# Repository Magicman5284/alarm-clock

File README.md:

Welcome to my alarm clock!

This project is an alarm clock that runs on an ESP32 and is controlled using an apple shortcut
The shortcut can be found here: https://www.icloud.com/shortcuts/9c18b0a72f074b27aea9341c8937683c

Features:
Set alarm
Set repeating alarm
View alarm list
cancel alarm
stopwatch
timer
cancel alarm

About the design:
The PCB has a bunch of little bits of text and images over because I decided to customize it
This is the third PCB I've made, and it's the first one I went all out on decorating. 
Look around for some of the easter eggs!

Use:
Useage is pretty simple, just run the short cut and it gives you prompts from there. 
your phone needs to be on the same wifi network in order to connect
Pressing the button does different thing depending on what mode the cock is in
When pressing it when the clock is at idle, it will display the next alarm. 
When pressing it while a stop watch is running it will stop the stopwatch
When pressing it while a timer is running it will stop the timer. 
And obviously when pressing it while an alarm is going off it will stop the alarm. 

Assembly:
before uploading code, make sure to input your wifi details into the software
put all components except for the switch on the side with the dog
put the switch on the other side
I'm not gonna bother explaining how to solder
next, put the screen in the screen hole of the housing
put the speaker in the speaker hole of the housing
Put the PCB in the housing, making sure to align the port on the ESP32 with the hole
put the lid on 
put the keycap on the switch
power it using the port on the esp32

BOM: 
| Item                     | Qty | Supplier   | Cost/item | Total Cost | link                                                                                                                                                                                                                                                                                                                                                                                                                                                                                                                                                                                                                                                                   |
|--------------------------|-----|------------|-----------|------------|------------------------------------------------------------------------------------------------------------------------------------------------------------------------------------------------------------------------------------------------------------------------------------------------------------------------------------------------------------------------------------------------------------------------------------------------------------------------------------------------------------------------------------------------------------------------------------------------------------------------------------------------------------------------|
| PCB                      | 1   | JLCPCB     | $11.75    | $11.75     | https://cart.jlcpcb.com/shopcart/cart/                                                                                                                                                                                                                                                                                                                                                                                                                                                                                                                                                                                                                                 |
| ESP32 Devkit 32e         | 1   | Aliexpress | $4.89     | $4.89      | https://www.aliexpress.us/item/3256806702153769.html?spm=a2g0o.productlist.main.18.67585c09bSFoCP&algo_pvid=f1ce53f9-d5df-4b3a-970c-3f98776b2e6a&algo_exp_id=f1ce53f9-d5df-4b3a-970c-3f98776b2e6a-17&pdp_ext_f=%7B%22order%22%3A%22350%22%2C%22eval%22%3A%221%22%2C%22fromPage%22%3A%22search%22%7D&pdp_npi=6%40dis%21USD%213.09%213.09%21%21%213.09%213.09%21%40210311c217933246971303026e0ffa%2112000038626150028%21sea%21US%212783459362%21X%211%210%21n_tag%3A-29919%3Bd%3Abaf43391%3Bm03_new_user%3A-29895&curPageLogUid=7mRbqkwcirtO&utparam-url=scene%3Asearch%7Cquery_from%3A%7Cx_object_id%3A1005006888468521%7C_p_origin_prod%3A                             |
| dfplayermini             | 1   | Aliexpress | $0.99     | $0.99      | https://www.aliexpress.us/w/wholesale-dfplayermi.html?spm=a2g0o.cart.search.0                                                                                                                                                                                                                                                                                                                                                                                                                                                                                                                                                                                          |
| 4 ohm 3 watt speaker     | 1   | Aliexpress | $1.55     | $1.55      | https://www.aliexpress.us/item/3256808440309449.html?spm=a2g0o.productlist.main.26.3e115336ekZqeb&algo_pvid=ed21cef5-22ef-4ecc-961e-e51a669bdb40&algo_exp_id=ed21cef5-22ef-4ecc-961e-e51a669bdb40-25&pdp_ext_f=%7B%22order%22%3A%225833%22%2C%22eval%22%3A%221%22%2C%22fromPage%22%3A%22search%22%7D&pdp_npi=6%40dis%21USD%215.25%214.25%21%21%215.25%214.25%21%402101e81117933248692643231e0f08%2112000046009599177%21sea%21US%212783459362%21X%211%210%21n_tag%3A-29919%3Bd%3Abaf43391%3Bm03_new_user%3A-29895%3BpisId%3A5000000219603055&curPageLogUid=h7SvuAxJD4rP&utparam-url=scene%3Asearch%7Cquery_from%3A%7Cx_object_id%3A1005008626624201%7C_p_origin_prod%3A |
| cherry mx switch         | 1   | Aliexpress | $2.27     | $2.27      | https://www.aliexpress.us/item/3256801976570526.html?spm=a2g0o.productlist.main.5.688744ccV9ucZ5&algo_pvid=7ed89fed-d3cb-4a07-b618-00326d9a45f0&algo_exp_id=7ed89fed-d3cb-4a07-b618-00326d9a45f0-4&pdp_ext_f=%7B%22order%22%3A%2292%22%2C%22eval%22%3A%221%22%2C%22fromPage%22%3A%22search%22%7D&pdp_npi=6%40dis%21USD%212.27%212.27%21%21%212.27%212.27%21%402103274a17933249592103766e0baa%2112000018919108208%21sea%21US%212783459362%21X%211%210%21n_tag%3A-29919%3Bd%3Abaf43391%3Bm03_new_user%3A-29895&curPageLogUid=fu1PsmRXaU1L&utparam-url=scene%3Asearch%7Cquery_from%3A%7Cx_object_id%3A1005002162885278%7C_p_origin_prod%3A                                |
| 1x2 dupont connector     | 1   | Aliexpress | $1.60     | $1.60      | https://www.aliexpress.us/item/3256811876826434.html?spm=a2g0o.productlist.main.25.623949597420vA&algo_pvid=894fe34e-67f8-4acd-bffa-2217c9a293bd&algo_exp_id=894fe34e-67f8-4acd-bffa-2217c9a293bd-22&pdp_ext_f=%7B%22order%22%3A%22579%22%2C%22eval%22%3A%221%22%2C%22fromPage%22%3A%22search%22%7D&pdp_npi=6%40dis%21USD%212.60%211.60%21%21%212.60%211.60%21%402101e5ab17933250643156929e0eb4%2112000057466932456%21sea%21US%212783459362%21X%211%210%21n_tag%3A-29919%3Bd%3Abaf43391%3Bm03_new_user%3A-29895%3BpisId%3A5000000219603055&curPageLogUid=lbAIQ25zZsG3&utparam-url=scene%3Asearch%7Cquery_from%3A%7Cx_object_id%3A1005012063141186%7C_p_origin_prod%3A  |
| 1x4 dupont connector     | 1   | Aliexpress | $1.85     | $1.85      | https://www.aliexpress.us/item/3256811876826434.html?spm=a2g0o.productlist.main.25.623949597420vA&algo_pvid=894fe34e-67f8-4acd-bffa-2217c9a293bd&algo_exp_id=894fe34e-67f8-4acd-bffa-2217c9a293bd-22&pdp_ext_f=%7B%22order%22%3A%22579%22%2C%22eval%22%3A%221%22%2C%22fromPage%22%3A%22search%22%7D&pdp_npi=6%40dis%21USD%212.60%211.60%21%21%212.60%211.60%21%402101e5ab17933250643156929e0eb4%2112000057466932456%21sea%21US%212783459362%21X%211%210%21n_tag%3A-29919%3Bd%3Abaf43391%3Bm03_new_user%3A-29895%3BpisId%3A5000000219603055&curPageLogUid=lbAIQ25zZsG3&utparam-url=scene%3Asearch%7Cquery_from%3A%7Cx_object_id%3A1005012063141186%7C_p_origin_prod%3A  |
| 1k resistor              | 1   | Aliexpress | $0.99     | $0.99      | https://www.aliexpress.us/item/2251832129610568.html?spm=a2g0o.productlist.main.1.25326d60rdNL8u&algo_pvid=edfc57ec-6b59-4211-b7e8-f2a065aece70&algo_exp_id=edfc57ec-6b59-4211-b7e8-f2a065aece70-0&pdp_ext_f=%7B%22order%22%3A%22717%22%2C%22eval%22%3A%221%22%2C%22fromPage%22%3A%22search%22%7D&pdp_npi=6%40dis%21USD%211.47%210.99%21%21%211.47%210.99%21%402103094f17933252044222206e0fe1%2158254850883%21sea%21US%212783459362%21X%211%210%21n_tag%3A-29919%3Bd%3Abaf43391%3Bm03_new_user%3A-29895%3BpisId%3A5000000219603055&curPageLogUid=x9bjduV6E75j&utparam-url=scene%3Asearch%7Cquery_from%3A%7Cx_object_id%3A32315925320%7C_p_origin_prod%3A               |
| 2.75u keycap             | 1   | Aliexpress | $5.95     | $5.95      | https://www.aliexpress.us/item/3256807398966945.html?spm=a2g0o.productlist.main.2.5a3e4688DaLE72&algo_pvid=579fe484-0437-467e-8f6a-9ced1f6fc345&algo_exp_id=579fe484-0437-467e-8f6a-9ced1f6fc345-1&pdp_ext_f=%7B%22order%22%3A%22775%22%2C%22eval%22%3A%221%22%2C%22fromPage%22%3A%22search%22%7D&pdp_npi=6%40dis%21USD%215.95%215.95%21%21%2139.43%2139.43%21%402103094f17933252657634725e0fe1%2112000041398778703%21sea%21US%212783459362%21X%211%210%21n_tag%3A-29919%3Bd%3Abaf43391%3Bm03_new_user%3A-29895&curPageLogUid=ulMywThyTcc5&utparam-url=scene%3Asearch%7Cquery_from%3A%7Cx_object_id%3A1005007585281697%7C_p_origin_prod%3A                             |
| MicroSD card             | 1   | Aliexpress | $4.69     | $4.69      | https://www.aliexpress.us/item/3256811941680244.html?spm=a2g0o.productlist.main.8.60f66b2efRxJoC&algo_pvid=11c2aabe-f7a2-40ce-a041-4d8680cf8152&algo_exp_id=11c2aabe-f7a2-40ce-a041-4d8680cf8152-7&pdp_ext_f=%7B%22order%22%3A%22122%22%2C%22eval%22%3A%221%22%2C%22fromPage%22%3A%22search%22%7D&pdp_npi=6%40dis%21USD%214.75%214.65%21%21%2131.48%2130.82%21%40210328df17933253806557798e0f2b%2112000057588136790%21sea%21US%212783459362%21X%211%210%21n_tag%3A-29919%3Bd%3Abaf43391%3Bm03_new_user%3A-29895&curPageLogUid=MspO1k5kvHQz&utparam-url=scene%3Asearch%7Cquery_from%3A%7Cx_object_id%3A1005012127994996%7C_p_origin_prod%3A                             |
| TM1637 display           | 1   | Aliexpress | $1.51     | $1.51      | https://www.aliexpress.us/item/3256802087257562.html?spm=a2g0o.productlist.main.13.6d5a753f3vqx8d&algo_pvid=2fb0a497-69e9-4dab-829a-9f21d02ad9ce&algo_exp_id=2fb0a497-69e9-4dab-829a-9f21d02ad9ce-12&pdp_ext_f=%7B%22order%22%3A%2234%22%2C%22eval%22%3A%221%22%2C%22fromPage%22%3A%22search%22%7D&pdp_npi=6%40dis%21USD%211.51%211.51%21%21%211.51%211.51%21%40210327ef17933255281251190e0cd9%2112000019863214642%21sea%21US%212783459362%21X%211%210%21n_tag%3A-29919%3Bd%3Abaf43391%3Bm03_new_user%3A-29895&curPageLogUid=QMSImAcfJLqn&utparam-url=scene%3Asearch%7Cquery_from%3A%7Cx_object_id%3A1005002273572314%7C_p_origin_prod%3A                              |
| Estimated total shipping | 1   |            |           | $0.00      |                                                                                                                                                                                                                                                                                                                                                                                                                                                                                                                                                                                                                                                                        |

Images:

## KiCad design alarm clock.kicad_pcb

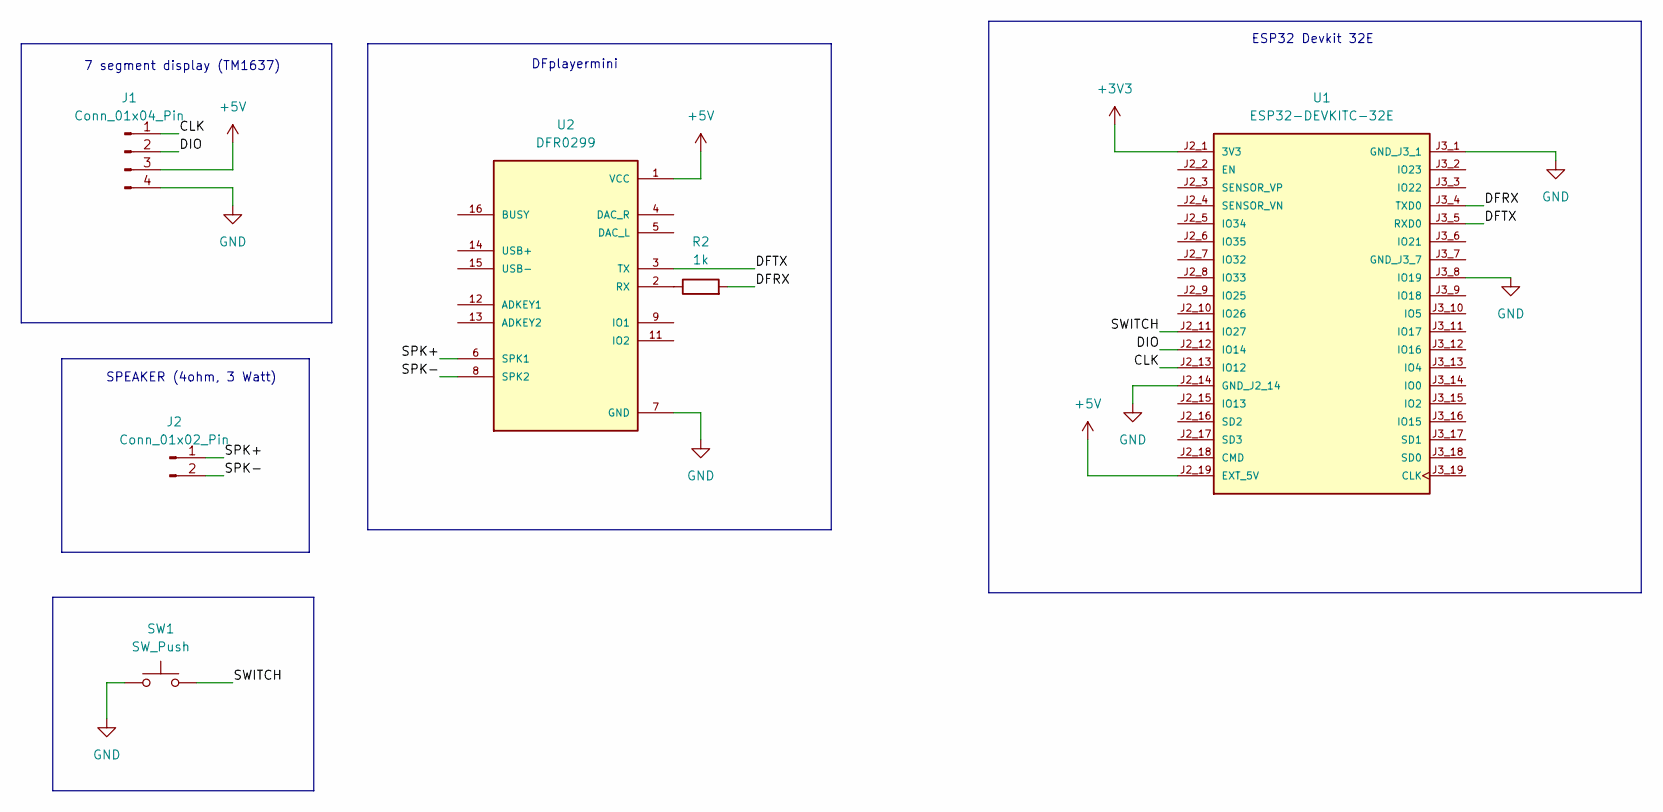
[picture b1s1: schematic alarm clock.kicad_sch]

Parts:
J1: Conn_01x04_Pin; PinSocket_1x04_P2.54mm_Vertical
J2: Conn_01x02_Pin; PinSocket_1x02_P2.54mm_Vertical
R2: 1k; R_Axial_DIN0204_L3.6mm_D1.6mm_P7.62mm_Horizontal
SW1: SW_Push; SW_Cherry_MX_1.00u_PCB
U1: ESP32-DEVKITC-32E; MODULE_ESP32-DEVKITC-32E; PARTREV 1.4
U2: DFR0299; MODULE_DFR0299; DigiKey_Part_Number 1738-1041-ND

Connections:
+3V3: U1.J2_1 (3V3)
+5V: J1.3, U1.J2_19 (EXT_5V), U2.1 (VCC)
/CLK: J1.1, U1.J2_13 (IO12)
/DFRX: R2.2, U1.J3_4 (TXD0)
/DFTX: U1.J3_5 (RXD0), U2.3 (TX)
/DIO: J1.2, U1.J2_12 (IO14)
/SPK+: J2.1, U2.6 (SPK1)
/SPK-: J2.2, U2.8 (SPK2)
/SWITCH: SW1.2, U1.J2_11 (IO27)
GND: J1.4, SW1.1, U1.J2_14 (GND_J2_14), U1.J3_1 (GND_J3_1), U1.J3_8 (IO19), U2.7 (GND), U2.10 (GND)
unnamed: R2.1, U2.2 (RX)

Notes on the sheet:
DFplayermini
7 segment display (TM1637)
SPEAKER (4ohm, 3 Watt)
ESP32 Devkit 32E

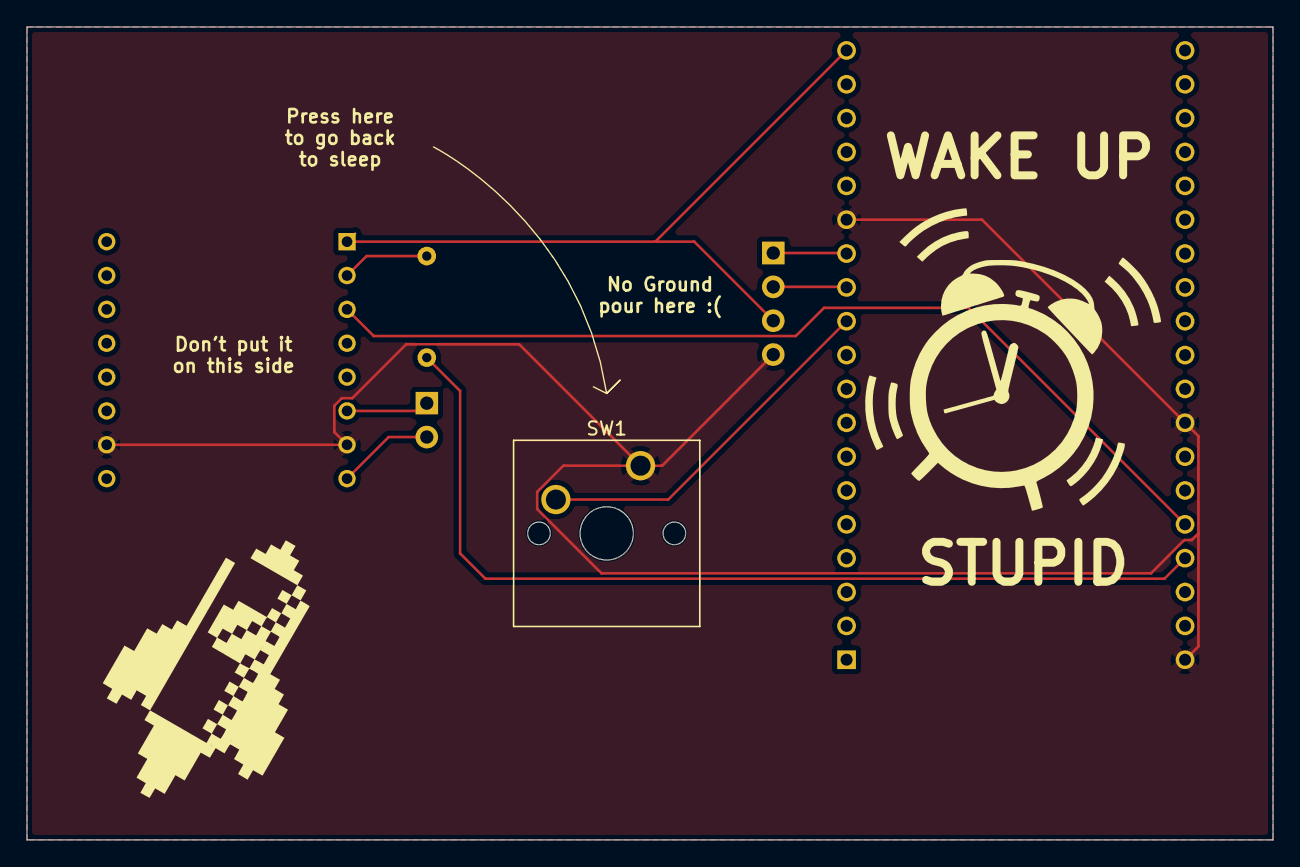
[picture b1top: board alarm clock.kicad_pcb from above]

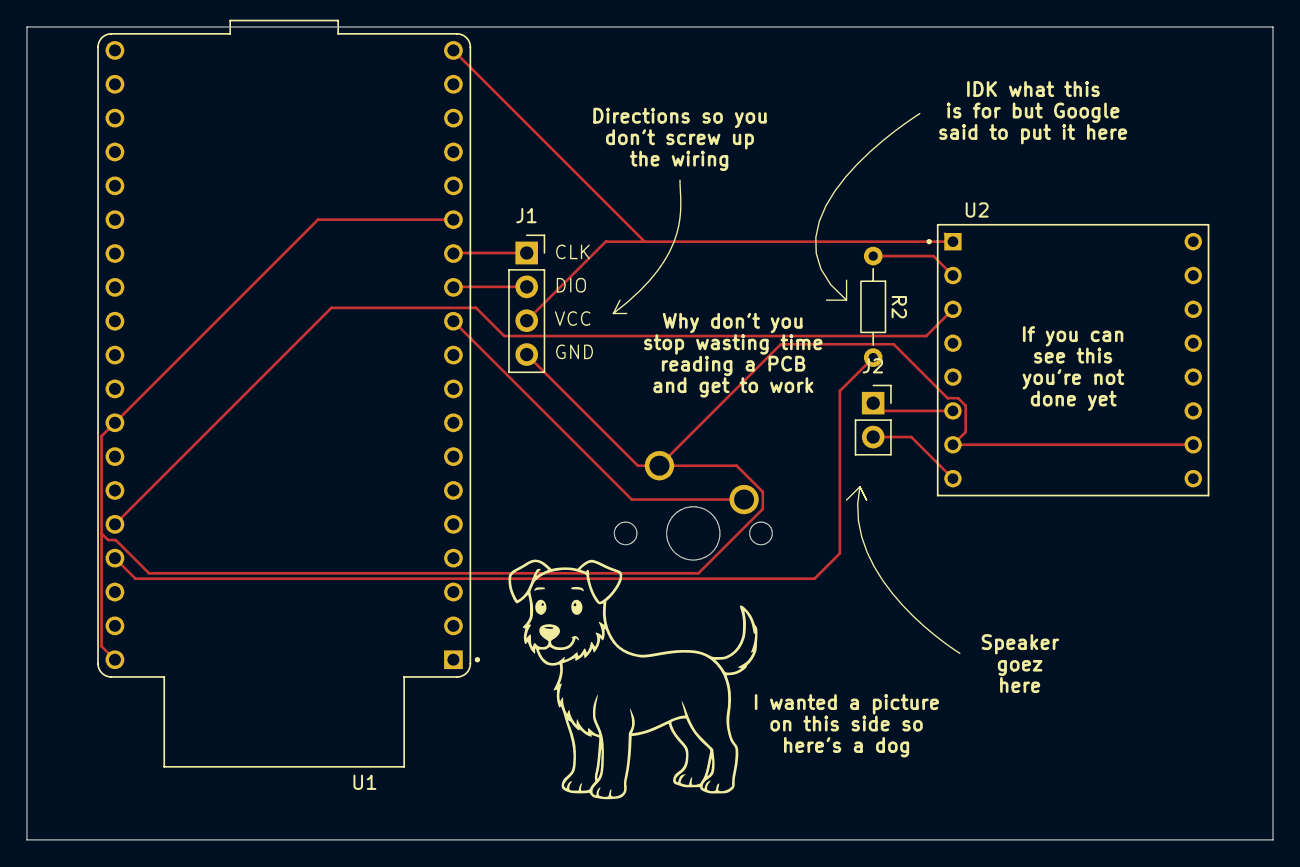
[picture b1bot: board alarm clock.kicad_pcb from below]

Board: 2 copper layers, 93.5 x 61.0 mm, 6 parts (5 on the bottom side), 10 nets.
